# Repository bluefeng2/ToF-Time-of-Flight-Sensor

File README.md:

# STM32 Distance Sensor Node
A compact distance-sensing project using the STM32F030 MCU and a VL53L0X Time-of-Flight (ToF) sensor. 

This was made to be used as a object detection sensor.

## 3D Model (CAD)

## PCB Design

## BOM (Bill of Materials)
| Item Name                             | Link    | Cost (CAD) | Amount | Total (CAD) |
| ------------------------------------- | ------- | ---------: | -----: | ----------: |
| Ceramic Capacitor 0.1 μF 50V X7R 0603 | Digikey |      0.011 |     10 |        0.11 |
| Ceramic Capacitor 4.7 μF 10V X5R 0603 | Digikey |      0.006 |     10 |        0.06 |
| LED Orange Clear Chip SMD             | Digikey |       0.11 |      5 |        0.55 |
| LED Red Clear Chip SMD                | Digikey |       0.12 |      5 |        0.60 |
| LED Green Clear Chip SMD              | Digikey |       0.12 |      6 |        0.60 |
| Connector Header R/A 3-Pos 2.54 mm    | Digikey |       0.93 |      3 |        2.79 |
| Resistor SMD 150 Ω 0.1% 1/10W 0603    | Digikey |      0.061 |     10 |        0.61 |
| Resistor SMD 4.7 kΩ 1% 1/10W 0603     | Digikey |      0.034 |     10 |        0.34 |
| Trimmer 100 kΩ J-Lead Top             | Digikey |       0.25 |      7 |        1.75 |
| MCU STM32F030F4P6 32-bit 16KB         | Digikey |       1.52 |      3 |        4.56 |
| Optical Sensor VL53L1CXV0FY/1         | Digikey |       5.77 |      3 |       17.31 |
| Linear Regulator MCP1703AT-3302E      | Digikey |       0.75 |      3 |        2.25 |
| Ceramic Capacitor 18 pF 250V C0G 0603 | Digikey |      0.157 |     10 |        1.57 |
| Crystal 8.000 MHz HC-49/U             | Digikey |       0.49 |      3 |        1.47 |
| Ceramic Capacitor 1 μF 10V X7R 0603   | Digikey |      0.005 |     10 |        0.05 |
| Switch Tactile SPST-NO                | Digikey |       0.60 |      3 |        1.80 |
| Digikey Shipping                      | Digikey |      20.00 |      1 |       20.00 |
| Custom PCB                            | JLCPCB  |       7.65 |      1 |        7.65 |
| **Total CAD**                         |         |            |        |   **64.07** |
| **Total USD**                         |         |            |        |   **46.72** |

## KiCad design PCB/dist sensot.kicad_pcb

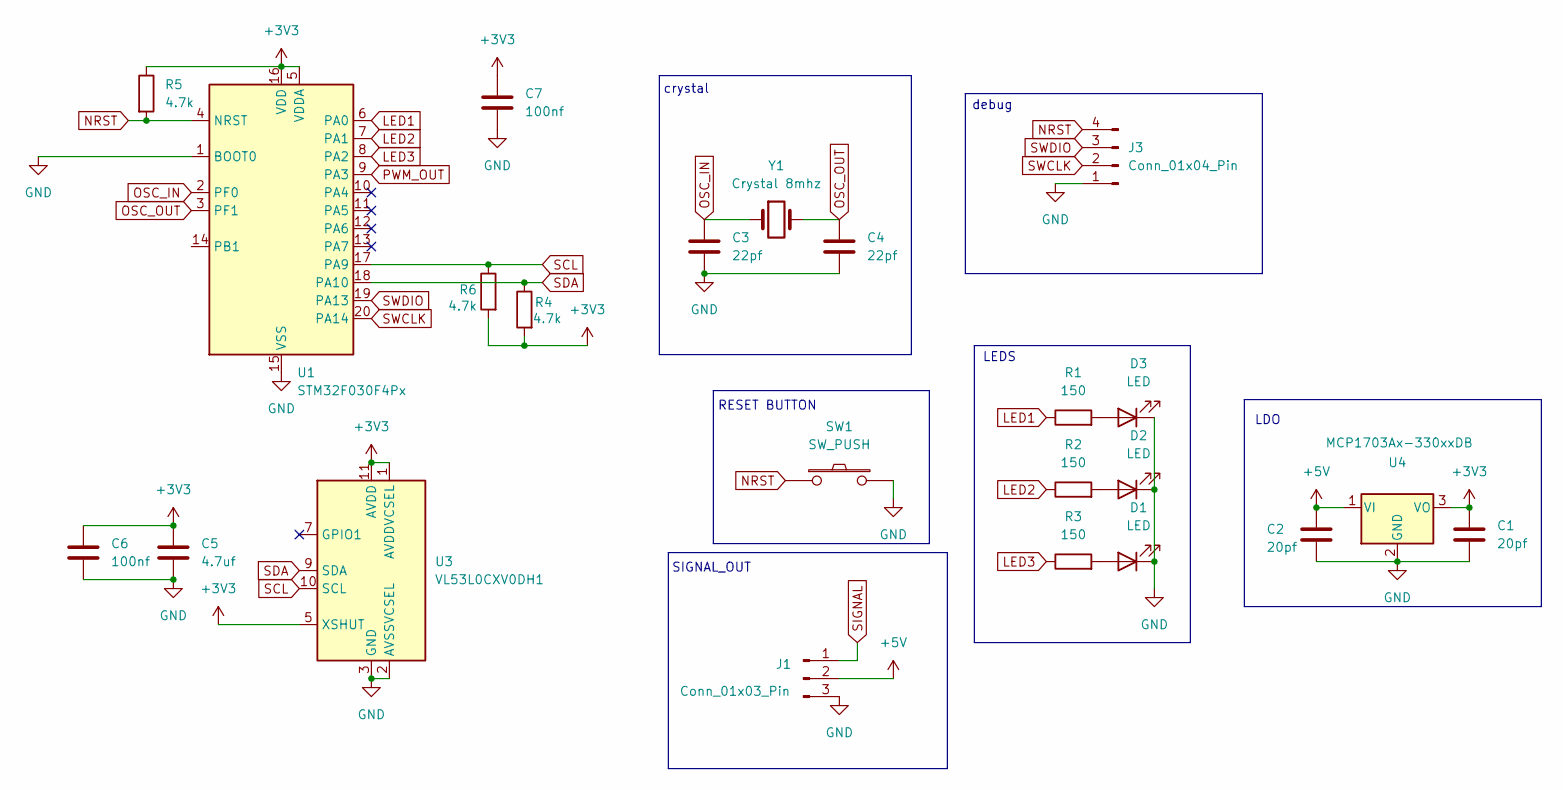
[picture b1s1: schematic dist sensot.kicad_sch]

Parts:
C1, C2: 20pf; C_0603_1608Metric
C3, C4: 22pf; C_0603_1608Metric
C5: 4.7uf; C_0603_1608Metric
C6, C7: 100nf; C_0603_1608Metric
D1, D2, D3: LED; LED_0603_1608Metric
J1: Conn_01x03_Pin; Molex_SL_171971-0003_1x03_P2.54mm_Vertical
J3: Conn_01x04_Pin; PinHeader_1x04_P2.54mm_Vertical
R1, R2, R3: 150; R_0603_1608Metric
R4, R5, R6: 4.7k; R_0603_1608Metric
SW1: SW_PUSH; SW_Push_SPST_NO_Alps_SKRK
U1: STM32F030F4Px; TSSOP-20_4.4x6.5mm_P0.65mm
U3: VL53L0CXV0DH1; ST_VL53L1x
U4: MCP1703Ax-330xxDB; SOT-223-3_TabPin2
Y1: Crystal 8mhz; Crystal_HC49-U_Vertical

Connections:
+3V3: C1.1, C5.1, C6.1, C7.1, R4.2, R5.1, R6.2, U1.5 (VDDA), U1.16 (VDD), U3.1 (AVDDVCSEL), U3.5 (XSHUT), U3.11 (AVDD), U4.3 (VO)
+5V: C2.1, J1.2, U4.1 (VI)
GND: C1.2, C2.2, C3.2, C4.2, C5.2, C6.2, C7.2, D1.1 (K), D2.1 (K), D3.1 (K), J1.3, J3.1, SW1.2, U1.1 (BOOT0), U1.15 (VSS), U3.2 (AVSSVCSEL), U3.3 (GND), U3.4 (GND), U3.6 (GND), U3.12 (GND), U4.2 (GND)
LED1: R1.1, U1.6 (PA0)
LED2: R2.1, U1.7 (PA1)
LED3: R3.1, U1.8 (PA2)
NRST: J3.4, R5.2, SW1.1, U1.4 (NRST)
unnamed: D1.2 (A), R3.2
unnamed: D2.2 (A), R2.2
unnamed: D3.2 (A), R1.2
OSC_IN: C3.1, U1.2 (PF0), Y1.1
OSC_OUT: C4.1, U1.3 (PF1), Y1.2
PWM_OUT: U1.9 (PA3)
SCL: R6.1, U1.17 (PA9), U3.10 (SCL)
SDA: R4.1, U1.18 (PA10), U3.9 (SDA)
SIGNAL: J1.1
SWCLK: J3.2, U1.20 (PA14)
SWDIO: J3.3, U1.19 (PA13)

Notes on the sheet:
SIGNAL_OUT
RESET BUTTON
debug
crystal
LDO
LEDS

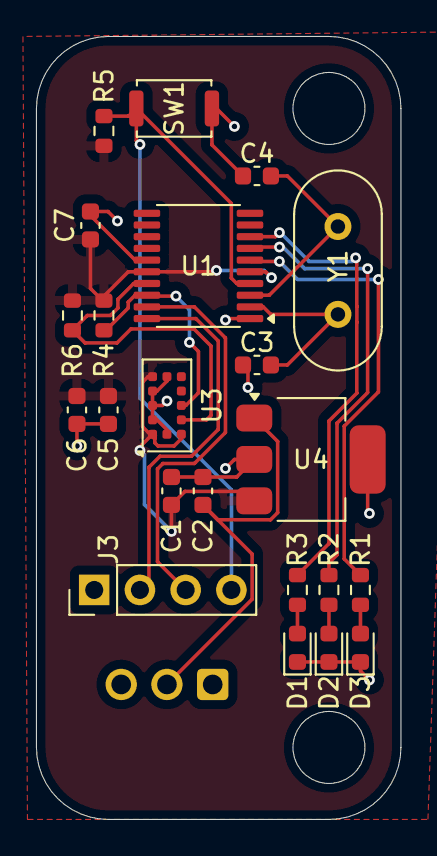
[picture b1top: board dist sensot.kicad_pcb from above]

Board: 2 copper layers, 20.2 x 43.5 mm, 23 parts (1 on the bottom side), 16 nets.

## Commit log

2026-01-26 upload
2026-05-14 Rename tof (3).zip to Gerbers.zip
